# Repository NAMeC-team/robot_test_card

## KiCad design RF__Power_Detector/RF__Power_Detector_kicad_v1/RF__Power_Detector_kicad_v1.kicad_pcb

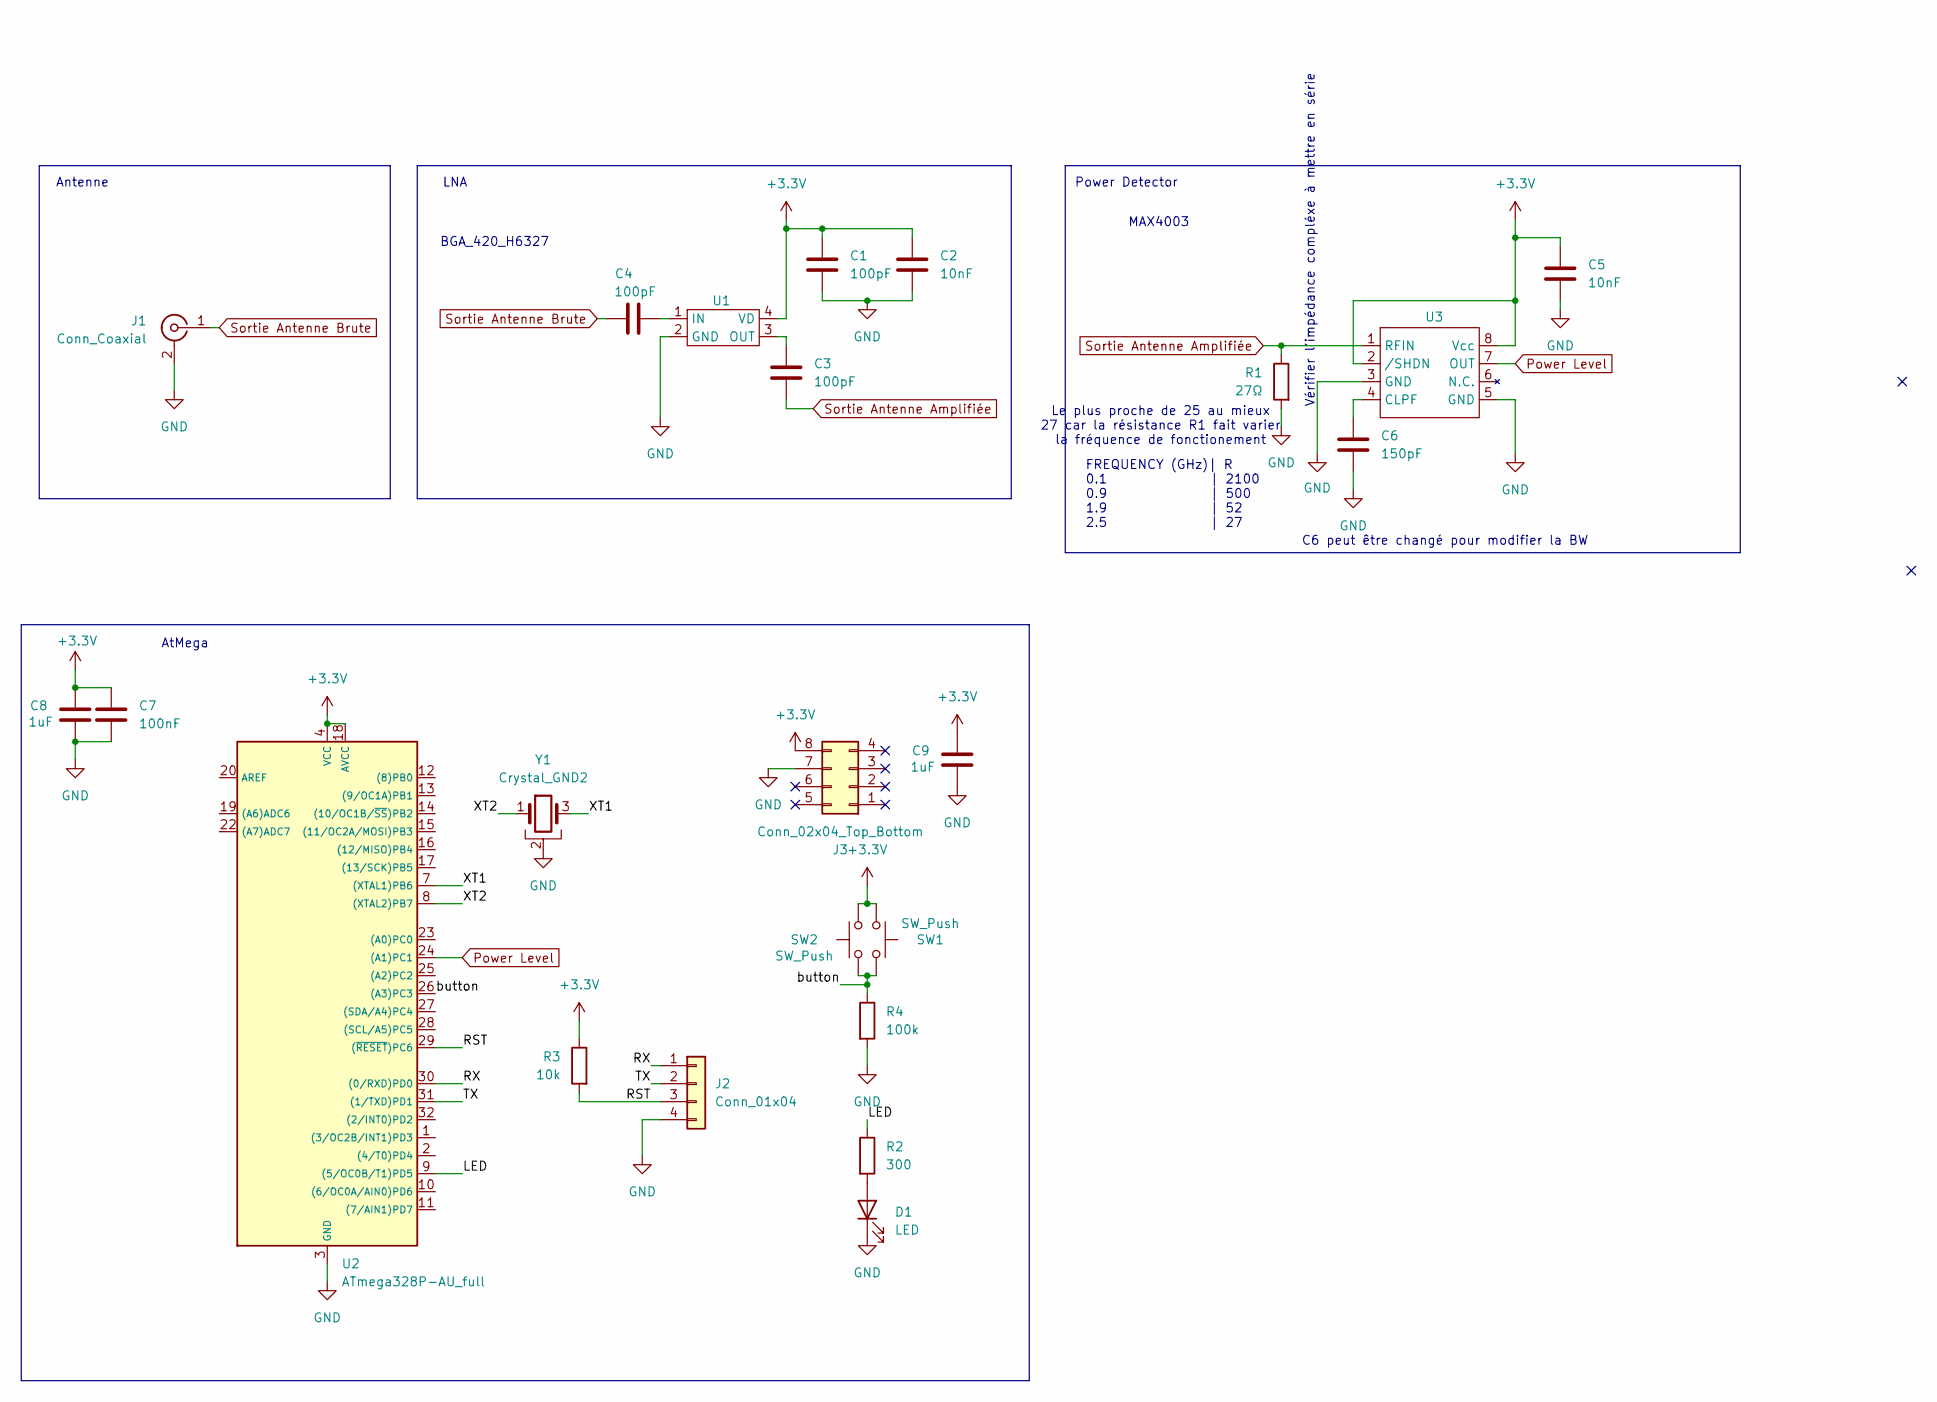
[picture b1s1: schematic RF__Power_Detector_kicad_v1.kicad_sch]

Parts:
C1, C3, C4: 100pF; C_0603_1608Metric
C2, C5: 10nF; C_0603_1608Metric
C6: 150pF; C_0603_1608Metric
C7: 100nF; C_0603_1608Metric
C8, C9: 1uF; C_0603_1608Metric
D1: LED; LED_1206_3216Metric
J1: Conn_Coaxial; SMA_BAT_Wireless_BWSMA-KWE-Z001
J2: Conn_01x04; PinHeader_1x04_P2.54mm_Vertical
J3: Conn_02x04_Top_Bottom; PinHeader_2x04_P2.54mm_Vertical
R1: 27Ω; R_0603_1608Metric_Pad0.98x0.95mm_HandSolder
R2: 300; R_0603_1608Metric_Pad0.98x0.95mm_HandSolder
R3: 10k; R_0603_1608Metric_Pad0.98x0.95mm_HandSolder
R4: 100k; R_0603_1608Metric_Pad0.98x0.95mm_HandSolder
SW1, SW2: SW_Push; sw_push_KMR2
U1: SOT343
U2: ATmega328P-AU_full; TQFP32m
U3: SOP65P490X110-8N
Y1: Crystal_GND2; osc_CSTCE

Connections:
+3.3V: C1.1, C2.1, C5.1, C7.1, C8.1, C9.1, J3.8, R3.1, SW1.2, SW2.1, U1.4 (VD), U2.4 (VCC), U2.6 (VCC), U2.18 (AVCC), U3.2 (/SHDN), U3.8 (Vcc)
/LED: R2.1, U2.9 ((5/OC0B/T1)PD5)
/RST: J2.3, R3.2, U2.29 ((~RESET)PC6)
/RX: J2.1, U2.30 ((0/RXD)PD0)
/TX: J2.2, U2.31 ((1/TXD)PD1)
/XT1: U2.7 ((XTAL1)PB6), Y1.3
/XT2: U2.8 ((XTAL2)PB7), Y1.1
/button: R4.1, SW1.1, SW2.2, U2.26 ((A3)PC3)
GND: C1.2, C2.2, C5.2, C6.2, C7.2, C8.2, C9.2, D1.1 (K), J1.2 (Ext), J2.4, J3.7, R1.2, R4.2, U1.2 (GND), U2.3 (GND), U2.5 (GND), U2.21 (GND), U3.3 (GND), U3.5 (GND), Y1.2
unnamed: D1.2 (A), R2.2
unnamed: C4.1, U1.1 (IN)
unnamed: C3.1, U1.3 (OUT)
unnamed: C6.1, U3.4 (CLPF)
Power Level: U2.24 ((A1)PC1), U3.7 (OUT)
Sortie Antenne Amplifiée: C3.2, R1.1, U3.1 (RFIN)
Sortie Antenne Brute: C4.2, J1.1 (In)

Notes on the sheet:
AtMega
Vérifier l'impédance compléxe à mettre en série
BGA_420_H6327
MAX4003
Le plus proche de 25 au mieux 27 car la résistance R1 fait varier la fréquence de fonctionement
FREQUENCY (GHz)| R 0.1 | 2100 0.9 | 500 1.9 | 52 2.5 | 27
Power Detector
Antenne
LNA
C6 peut être changé pour modifier la BW

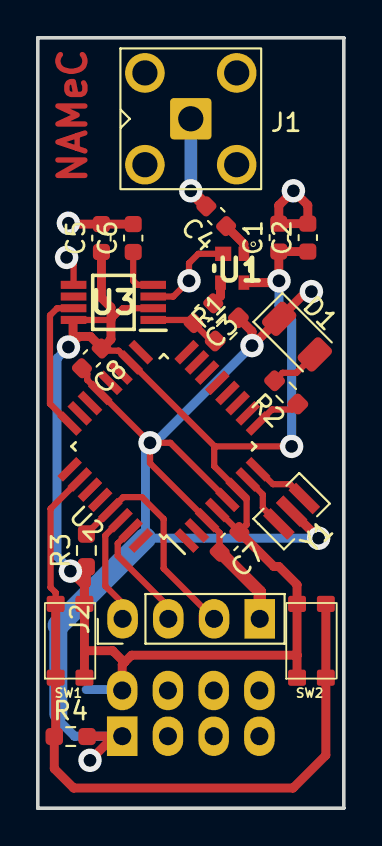
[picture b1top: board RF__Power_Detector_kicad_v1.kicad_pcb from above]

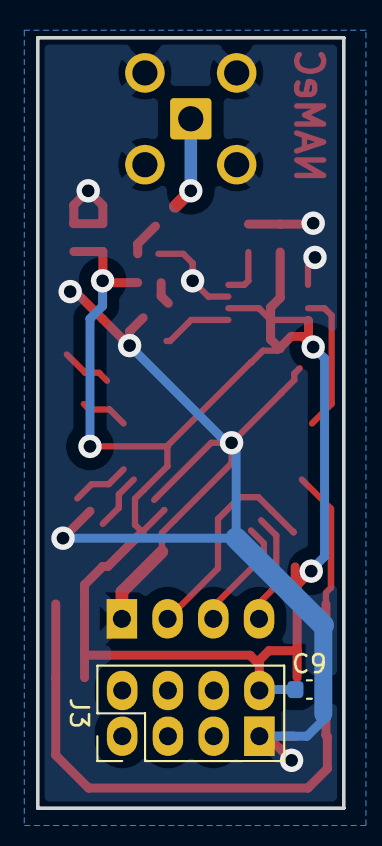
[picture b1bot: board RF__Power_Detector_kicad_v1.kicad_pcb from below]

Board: 2 copper layers, 17.0 x 42.8 mm, 23 parts (2 on the bottom side), 16 nets.

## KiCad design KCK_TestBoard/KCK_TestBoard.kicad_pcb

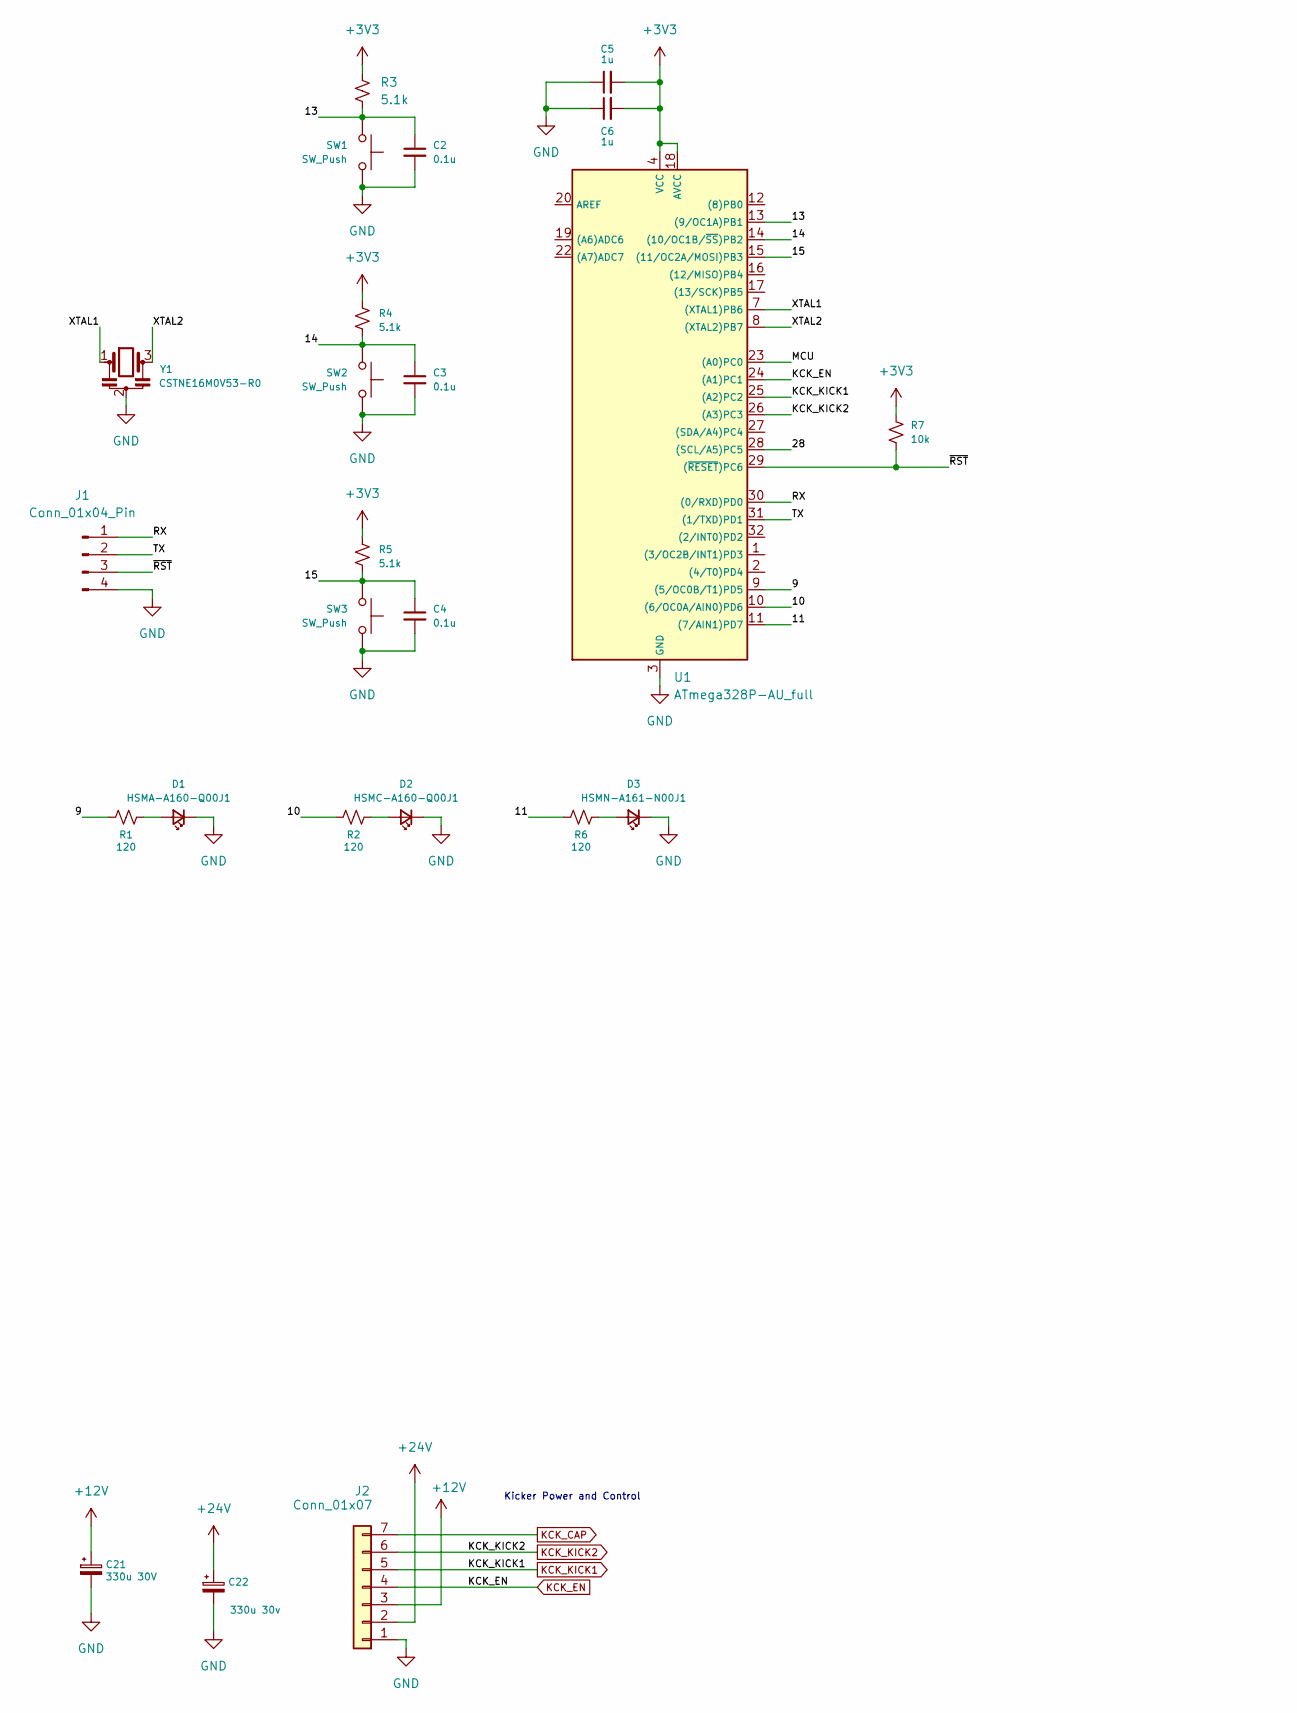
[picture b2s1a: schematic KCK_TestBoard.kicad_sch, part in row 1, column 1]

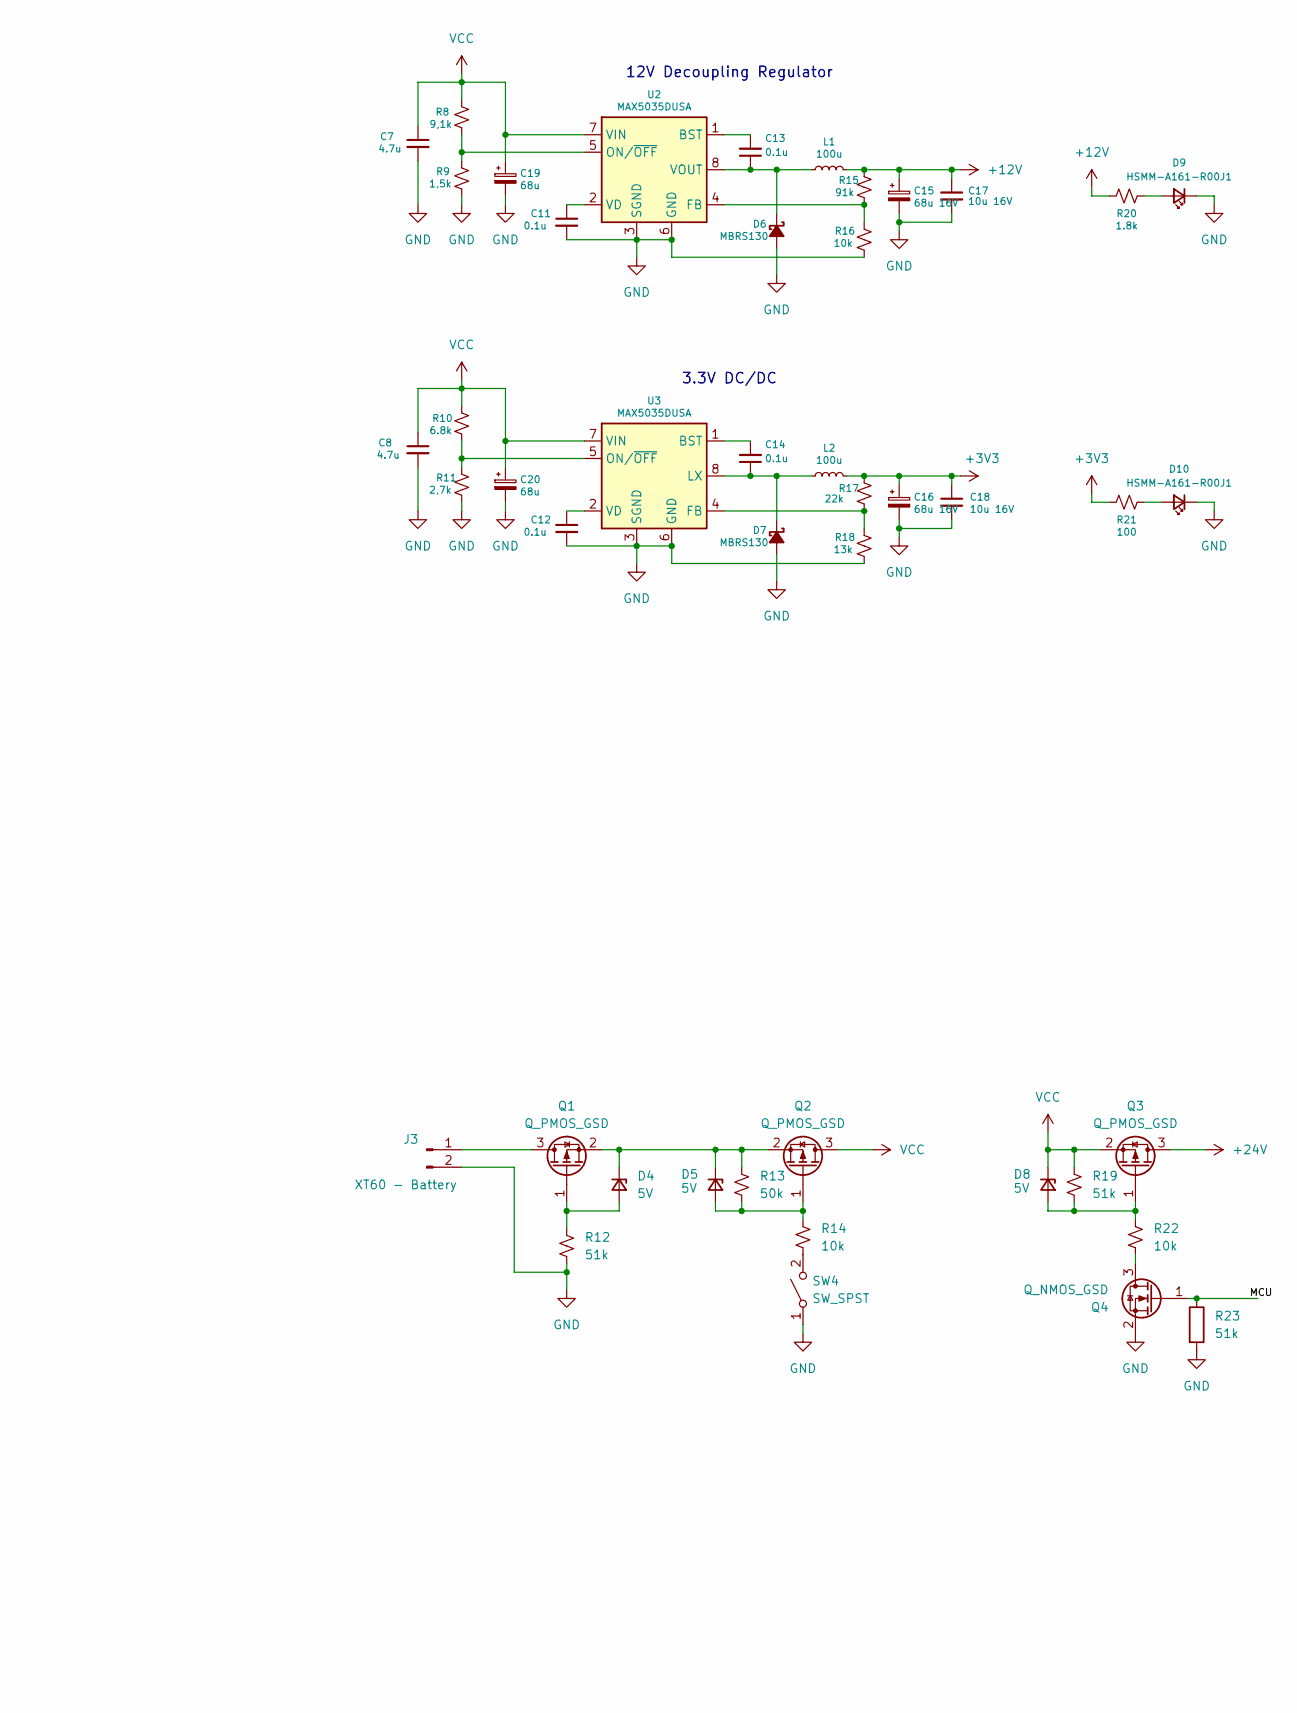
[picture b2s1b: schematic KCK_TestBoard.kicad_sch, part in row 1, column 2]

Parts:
C2, C3, C4, C11, C12, C13, C14: 0.1u; C_0603_1608Metric_Pad1.08x0.95mm_HandSolder
C5, C6: 1u; C_0603_1608Metric_Pad1.08x0.95mm_HandSolder
C7, C8: 4.7u; C_0603_1608Metric_Pad1.08x0.95mm_HandSolder
C15, C16: 68u 16V; CP_Radial_D5.0mm_P2.00mm
C17, C18: 10u 16V; C_1206_3216Metric
C19, C20: 68u; CP_Radial_D5.0mm_P2.00mm
C21: 330u 30V; CP_Radial_D12.5mm_P5.00mm
C22: 330u 30v; CP_Radial_D12.5mm_P5.00mm
D1: HSMA-A160-Q00J1; LED_1206_3216Metric
D2: HSMC-A160-Q00J1; LED_1206_3216Metric
D3: HSMN-A161-N00J1; LED_1206_3216Metric
D4, D5, D8: 5V; D_SOD-323_HandSoldering
D6, D7: MBRS130; D_SMB_Handsoldering
D9, D10: HSMM-A161-R00J1; LED_1206_3216Metric
J1: Conn_01x04_Pin; PinHeader_1x04_P2.54mm_Vertical
J2: Conn_01x07; JST_ZH_B7B-ZR_1x07_P1.50mm_Vertical
J3: XT60 - Battery; AMASS_XT60-M_1x02_P7.20mm_Vertical
L1, L2: 100u
Q1, Q2, Q3: Q_PMOS_GSD; TSOT-23
Q4: Q_NMOS_GSD; TSOT-23
R1, R2, R6: 120; R_0603_1608Metric_Pad0.98x0.95mm_HandSolder
R3, R4, R5: 5.1k; R_0603_1608Metric_Pad0.98x0.95mm_HandSolder
R7, R14, R16, R22: 10k; R_0603_1608Metric_Pad0.98x0.95mm_HandSolder
R8: 9,1k; R_0603_1608Metric_Pad0.98x0.95mm_HandSolder
R9: 1,5k; R_0603_1608Metric_Pad0.98x0.95mm_HandSolder
R10: 6.8k; R_0603_1608Metric_Pad0.98x0.95mm_HandSolder
R11: 2,7k; R_0603_1608Metric_Pad0.98x0.95mm_HandSolder
R12, R19, R23: 51k; R_0603_1608Metric_Pad0.98x0.95mm_HandSolder
R13: 50k; R_0603_1608Metric_Pad0.98x0.95mm_HandSolder
R15: 91k; R_0603_1608Metric_Pad0.98x0.95mm_HandSolder
R17: 22k; R_0603_1608Metric_Pad0.98x0.95mm_HandSolder
R18: 13k; R_0603_1608Metric_Pad0.98x0.95mm_HandSolder
R20: 1.8k; R_0603_1608Metric_Pad0.98x0.95mm_HandSolder
R21: 100; R_0603_1608Metric_Pad0.98x0.95mm_HandSolder
SW1, SW2, SW3: SW_Push
SW4: SW_SPST; SW_SPST_China
U1: ATmega328P-AU_full; TQFP32m
U2, U3: MAX5035DUSA; SOIC-8_3.9x4.9mm_P1.27mm
Y1: CSTNE16M0V53-R0; osc_CSTNE

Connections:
+3V3: C5.2, C6.2, C16.1, C18.1, L2.2, R3.1, R4.1, R5.1, R7.1, R17.1, R21.1, U1.4 (VCC), U1.6 (VCC), U1.18 (AVCC)
+12V: C15.1, C17.1, C21.1, J2.3, L1.2, R15.1, R20.1; also elsewhere on the board
/9: R1.1, U1.9 ((5/OC0B/T1)PD5)
/10: R2.1, U1.10 ((6/OC0A/AIN0)PD6)
/11: R6.1, U1.11 ((7/AIN1)PD7)
/13: C2.1, R3.2, SW1.1, U1.13 ((9/OC1A)PB1)
/14: C3.1, R4.2, SW2.1, U1.14 ((10/OC1B/~SS)PB2)
/15: C4.1, R5.2, SW3.1, U1.15 ((11/OC2A/MOSI)PB3)
/28: U1.28 ((SCL/A5)PC5)
/MCU: Q4.1 (G), R23.1, U1.23 ((A0)PC0)
/RX: J1.1, U1.30 ((0/RXD)PD0)
/TX: J1.2, U1.31 ((1/TXD)PD1)
/XTAL1: U1.7 ((XTAL1)PB6), Y1.1
/XTAL2: U1.8 ((XTAL2)PB7), Y1.3
/~RST: J1.3, R7.2, U1.29 ((~RESET)PC6)
GND: C2.2, C3.2, C4.2, C5.1, C6.1, C7.2, C8.2, C11.2, C12.2, C15.2, C16.2, C17.2, C18.2, C19.2, C20.2, C21.2, C22.2, D1.1 (K), D2.1 (K), D3.1 (K), D6.2 (A), D7.2 (A), D9.1 (K), D10.1 (K), J1.4, J2.1, J3.2, Q4.2 (S), R9.2, R11.2, R12.2, R16.2, R18.2, R23.2, SW1.2, SW2.2, SW3.2, SW4.1 (A), U1.3 (GND), U1.5 (GND), U1.21 (GND), U2.3 (SGND), U2.6 (GND), U3.3 (SGND), U3.6 (GND), Y1.2; also elsewhere on the board
KCK_CAP: J2.7
KCK_EN: J2.4, U1.24 ((A1)PC1)
KCK_KICK1: J2.5, U1.25 ((A2)PC2)
KCK_KICK2: J2.6, U1.26 ((A3)PC3)
unnamed: D1.2 (A), R1.2
unnamed: D2.2 (A), R2.2
unnamed: D3.2 (A), R6.2
unnamed: D4.2 (A), Q1.1 (G), R12.1
unnamed: D4.1 (K), D5.1 (K), Q1.2 (S), Q2.2 (S), R13.1
unnamed: D5.2 (A), Q2.1 (G), R13.2, R14.1
unnamed: C13.1, D6.1 (K), L1.1, U2.8 (VOUT)
unnamed: C14.1, D7.1 (K), L2.1, U3.8 (LX)
unnamed: D8.2 (A), Q3.1 (G), R19.2, R22.1
unnamed: D9.2 (A), R20.2
unnamed: D10.2 (A), R21.2
unnamed: J3.1, Q1.3 (D)
unnamed: Q4.3 (D), R22.2
unnamed: R14.2, SW4.2 (B)
unnamed: C13.2, U2.1 (BST)
unnamed: R15.2, R16.1, U2.4 (FB)
unnamed: R8.1, R9.1, U2.5 (ON/~OFF)
unnamed: C11.1, U2.2 (VD)
unnamed: C14.2, U3.1 (BST)
unnamed: R17.2, R18.1, U3.4 (FB)
unnamed: R10.1, R11.1, U3.5 (ON/~OFF)
unnamed: C12.1, U3.2 (VD)

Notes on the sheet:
3.3V DC/DC
12V Decoupling Regulator
Kicker Power and Control

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
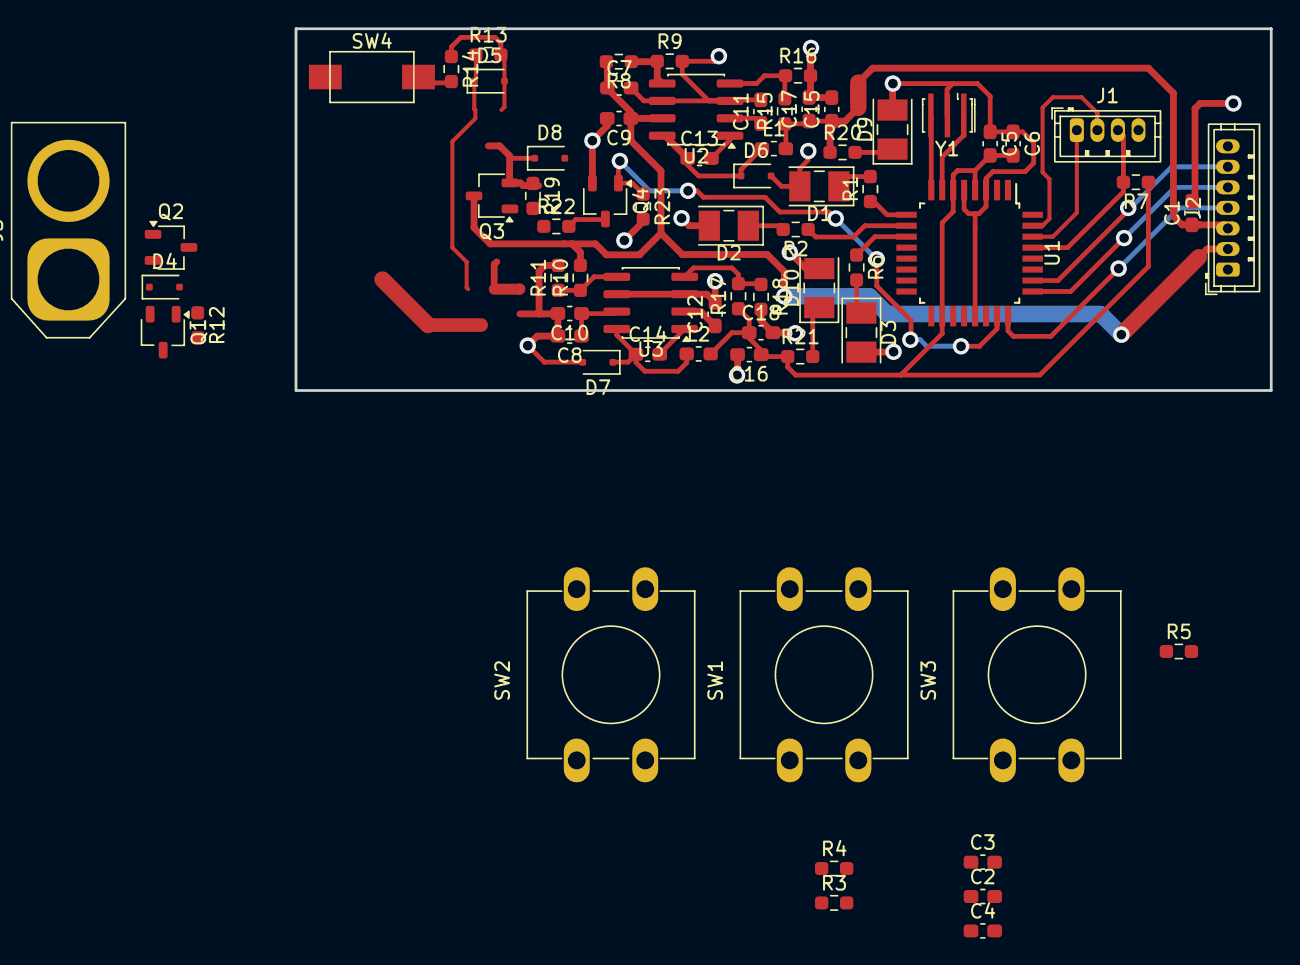
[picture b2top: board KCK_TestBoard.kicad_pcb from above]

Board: 2 copper layers, 71.2 x 26.4 mm, 68 parts (0 on the bottom side), 43 nets.

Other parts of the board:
C1: 1000u; C_0603_1608Metric_Pad1.08x0.95mm_HandSolder
C9, C10: 68u; C_0603_1608Metric_Pad1.08x0.95mm_HandSolder

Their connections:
+12V: C1.1; also elsewhere on the board
GND: C1.2, C9.2, C10.2; also elsewhere on the board
